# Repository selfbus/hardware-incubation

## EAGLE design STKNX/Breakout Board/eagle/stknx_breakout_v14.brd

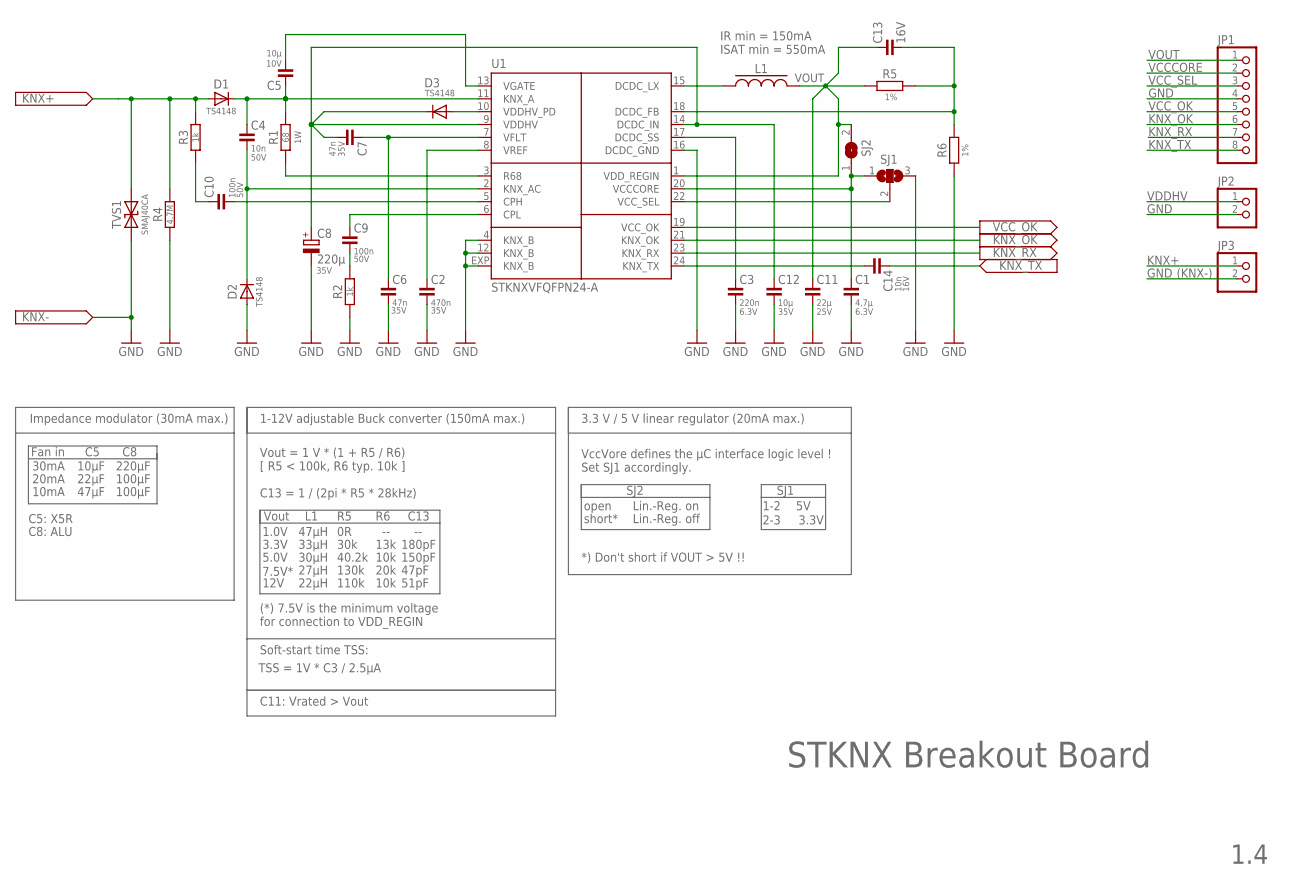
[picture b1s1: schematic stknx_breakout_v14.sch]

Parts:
C1: 4,7µ; C0805; VOLTAGE 6.3V
C2: 470n; C0805; VOLTAGE 35V
C3: 220n; C0805; VOLTAGE 6.3V
C4: 10n; C0805; VOLTAGE 50V
C5: 10µ; C0805; VOLTAGE 10V
C6, C7: 47n; C0805; VOLTAGE 35V
C8: 220µ; PANASONIC_F; VOLTAGE 35V
C9, C10: 100n; C0805; VOLTAGE 50V
C11: 22µ; C0805; VOLTAGE 25V
C12: 10µ; C0805; VOLTAGE 35V
C13: C13; C0805; VOLTAGE 16V
C14: 10n; C0805; VOLTAGE 16V
D1, D2, D3: TS4148; 0805
JP1: PINHD-1X8; 1X08
JP2, JP3: PINHD-1X2; 1X02
L1: L1; WE-LQS_4025
R1: 68; R2512
R2, R3: 1k; R0805
R4: 4.7M; R0805
R5: R5; R0805; TOLERANCE 1%
R6: R6; R0805; TOLERANCE 1%
SJ1: SJ2W; SJ_2W
SJ2: SJW
TVS1: SMAJ40CA; DO-214AC(SMA)
U1: STKNXVFQFPN24-A; VFQFPN24-A

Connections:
DCDC_FB: C13.2, R5.2, R6.2, U1.18 (DCDC_FB)
DCDC_SS: C3.1, U1.17 (DCDC_SS)
GND: C1.2, C2.2, C3.2, C6.2, C8.-, C11.2, C12.2, D2.A, JP1.4, JP2.2, JP3.2, R2.1, R4.1, R6.1, SJ1.3, TVS1.2 (A2), U1.4 (KNX_B), U1.12 (KNX_B), U1.16 (DCDC_GND), U1.EXP (KNX_B)
KNX+: D1.A, JP3.1, R3.2, R4.2, TVS1.1 (A1)
KNX_OK: JP1.6, U1.21 (KNX_OK)
KNX_RX: JP1.7, U1.23 (KNX_RX)
KNX_TX: C14.2, JP1.8
KNX_TX_1: C14.1, U1.24 (KNX_TX)
unnamed: C2.1, U1.8 (VREF)
unnamed: C6.1, C7.1, U1.7 (VFLT)
unnamed: R1.1, U1.3 (R68)
unnamed: C4.2, D2.C, U1.2 (KNX_AC)
unnamed: C4.1, C5.1, D1.C, R1.2, U1.11 (KNX_A)
unnamed: D3.A, U1.10 (VDDHV_PD)
unnamed: C9.2, R2.2
unnamed: C9.1, U1.6 (CPL)
unnamed: C10.1, R3.1
unnamed: C10.2, U1.5 (CPH)
unnamed: L1.1, U1.15 (DCDC_LX)
VCCCORE: C1.1, JP1.2, SJ1.1, SJ2.1, U1.20 (VCCCORE)
VCC_OK: JP1.5, U1.19 (VCC_OK)
VCC_SEL: JP1.3, SJ1.2, U1.22 (VCC_SEL)
VDDHV: C7.2, C8.+, C12.1, D3.C, JP2.1, U1.9 (VDDHV), U1.14 (DCDC_IN)
VGATE: C5.2, U1.13 (VGATE)
VOUT: C11.1, C13.1, JP1.1, L1.2, R5.1, SJ2.2, U1.1 (VDD_REGIN)

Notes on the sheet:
SJ1
1-2
2-3
3.3V
5.0V
7.5V*
12V
33µH
27µH
22µH
30µH
SJ2
open
short*
Lin.-Reg. on
Lin.-Reg. off
Vout
C13
30k
13k
180pF
1.4
STKNX Breakout Board
Vout = 1 V * (1 + R5 / R6) [ R5 < 100k, R6 typ. 10k ] C13 = 1 / (2pi * R5 * 28kHz)
VccVore defines the µC interface logic level ! Set SJ1 accordingly.
1.0V
47µH
(*) 7.5V is the minimum voltage for connection to VDD_REGIN
40.2k
10k
150pF
130k
20k
47pF
110k
51pF
Soft-start time TSS:
3.3 V / 5 V linear regulator (20mA max.)
1-12V adjustable Buck converter (150mA max.)
TSS = 1V * C3 / 2.5µA

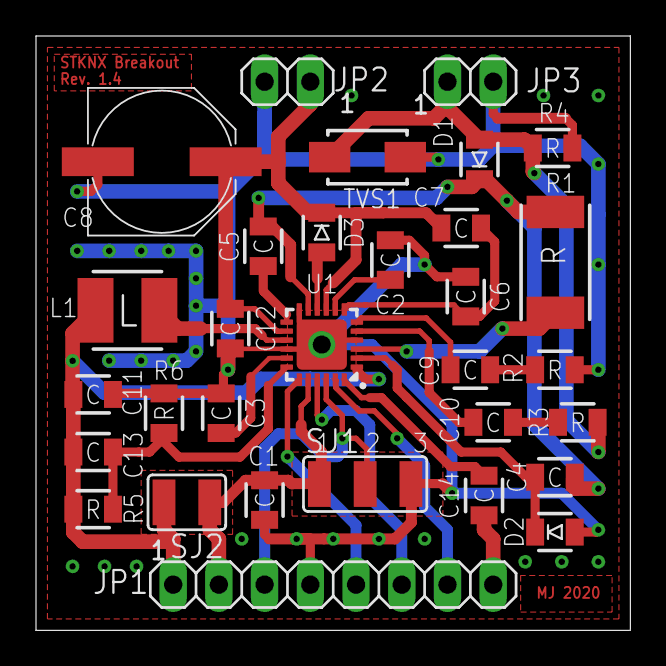
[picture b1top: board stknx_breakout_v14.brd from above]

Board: 2 copper layers, 33.0 x 33.0 mm, 31 parts (0 on the bottom side), 25 nets.
